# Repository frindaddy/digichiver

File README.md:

# Digichiver

Digichiver is an open hardware and software platform used for operation and 
archiving the audio output of the National Semiconductor MM54104 Mozer 
Digitalker speech synthesis system. The board can drive a physical MM54104,
serve historical speech ROM images through an RP2354B-based ROM emulator, and
record the resulting audio to a microSD card. Archived audio outputs are
available in the [Digitalker audio archive repository](https://github.com/frindaddy/digitalker-audio-archive).

## Repository Layout

The repository is organized by the part of the project it describes:

- `Hardware/` contains the KiCad schematics, PCB layout, custom footprints,
	fabrication outputs, and hardware design notes. Start with
	[`Hardware/readme.md`](Hardware/readme.md) for the circuit description.
- `Software/` contains the MicroPython firmware modules, ROM images, speech
	dictionaries, and archive configuration. Start with
	[`Software/readme.md`](Software/readme.md) for deployment and operation.
- `Simulation/` contains LTspice simulations for the analog speech filter.
- `DesignDocs/` contains project requirements and system architecture notes.
- `Datasheets/` contains component and reference documentation used by the
	design.
- `LICENSE` contains the project license.

## Using Digichiver

Digichiver requires the assembled board, an MM54104 Digitalker chip, and the
required ROM files for the speech vocabulary being used. The board is powered
and programmed over USB-C. Install the supplied
`Software/digichiver_firmware.uf2` firmware using the RP2354B USB bootloader,
then copy the required Python modules, ROM images, and JSON dictionaries from
`Software/` to the board's MicroPython filesystem.

After reset, connect to the board's MicroPython REPL. The software starts an
interactive `digichiver>` command loop for loading ROMs, speaking words,
checking word indexes, and archiving ROM groups to an inserted microSD card.
The complete command reference and file-deployment requirements are documented
in [`Software/readme.md`](Software/readme.md).

The hardware design can be opened with KiCad. The firmware `digitalker_firmware.u2f`
targets MicroPython on the RP2354B.

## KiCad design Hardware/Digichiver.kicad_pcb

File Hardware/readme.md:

# Circuit Description

The doc describes the digichicver circuit schematic (and PCB layout, when needed).

## Block Diagram

This sheet show the block diagram for the Digichiver board. The sheet is broken into 4 sections, the USB-C power/data connector, the Control block, the Digitalker block, the Audio block, and the Power block.

The USB-C connector is setup for a USB 2.0 full-speed connection, as that is the max capability of the RP2354B. Two $5.1k\Omega$ resistors tie `CC1` and `CC2` to ground to specify that this board is a power sink, per the USB specification. This advertises that this board can consume a maximum of 2.5W (5V@500mA).

## Control

This sheet shows the RP2354B and microSD card, as well as their supporting circuitry and pinouts.

### RP2354B

The RP2354B is the MCU on the Digichiver board and is used to control the MM54104 Digitalker chip, emulate Digitalker ROM modules, and record the Digitalker output audio to the microSD card (plus other basic GPIO functions). It interfaces with the MM54104 Digitalker chip, microSD card, and the PCM1809 audio recorder. The RP2354B has 2MB of internal flash in chip, so an external flash module is not required for operation.

#### RP2354B Power and Decoupling

The RP2354B nominally runs off a +3V3 supply, but requires a +1V1 rail for internal functions. Unlike its predecessor (the RP2340), the RP2354B ships with a built in switching regulator to generate this +1V1 rail in package, with the help of some supporting components. The design and layout of this power supply is strictly defined in [Hardware Design with the RP2350](https://pip-assets.raspberrypi.com/categories/1214-rp2350/documents/RP-008280-DS-1-hardware-design-with-rp2350.pdf), and the design recommendations were replicated here (part selection, connections, and layout).

Decoupling capacitors were placed based on the recommendations of [Hardware Design with the RP2350](https://pip-assets.raspberrypi.com/categories/1214-rp2350/documents/RP-008280-DS-1-hardware-design-with-rp2350.pdf); one for each power pin, and a special 4.7uF bulk cap for the +1V1 rail.

#### RP2354B USB Connection

The RP2354B is only capable of USB full speed (USB 2.0, 12Mbps, 48MHz clock). Though this is pretty slow speed, an attempt was made to keep the characteristic impedance of the USB traces close to the USB specification of $90\Omega$, differential. This board isn't being built with controlled impedances, so *rough* numbers are used for the calculation. To find the required trace width for a $90\Omega$ differential impedance, $Z_d$, we use the edge-coupled microstrip impedance equation.

$$Z_d \approx \frac{174}{\sqrt{\epsilon_r + 1.41}} \times \ln(\frac{5.98h}{0.8w + t}) \times [1-0.48^{-0.96\frac{s}{h}}]$$

where $Z_d$ is the differential impedance, $t$ is the trace thickness, $h$ is the height of the dielectric between the microstrip and ground plane, $s$ is the trace spacing, $\epsilon_r$ is the dielectric constant of the material, and $w$ is the trace width. The rough numbers are derived from the general JLCPCB 4 layer TG135 stackup and their manufacturing capabilities: $Z_d = 90\Omega$, $t = 1oz/ft^2$, $h = 8.283mil$, $s = 10mil$, and $\epsilon_r = 4.5$. Using these numbers, we calulate that the ideal trace width to achieve a $90\Omega$ differential impedance is `12.3645mil`.

$27\Omega$ series termination resistors are placed on the USB lines close to the RP2354B to meet the USB impedance specification.

#### RP2354B Clock

The RP2354B does not need an external clock to function (it ships with an internal oscillator), but a stable external frequency source greatly improves peripheral reliability and performance. As such, an external 12MHz crystal oscillator is used to clock the RP2354B. Part selection and circuit design are from the recommendations in [Hardware Design with the RP2350](https://pip-assets.raspberrypi.com/categories/1214-rp2350/documents/RP-008280-DS-1-hardware-design-with-rp2350.pdf).

#### Programming and Reset

Two pushbuttons, `SW1` and `SW2` are used to program and reset the RP2354B, respectively. When `SW1` is pressed on power up, the `QSPI_SS` line to the RP2354B is driven low, placing the device into programming mode. It will show up as a USB storage device, and a bootloader can be loaded into internal memory.

During operation, `SW2` can be pressed to reset the RP2354B by driving the `RUN` pin low.

#### Interfaces and GPIO

The MM54104 Digitalker control and ROM emulation busses take up most of the GPIO pins on the RP2354B. These signals are broken out as follows:

MM54104 Control Signals

| Signal | I/O | Pin Count |
| ------ | --- | --------- |
| SPC Word Selection Bus | O | 8 |
| SPC Chip Select | O | 1 |
| SPC Command Select | O | 1 |
| SPC Write Strobe | O | 1 |
| SPC Interrupt | I | 1 |

MM54104 ROM Emulation

| Signal | I/O | Pin Count |
| ------ | --- | --------- |
| ROM Address Bus | I | 14 |
| ROM Data Bus | O | 8 |
| ROMEN | I | 1 |

Because the MM54104 operates on +5V logic levels, these signals require level shifting. The level shifters are found on the Digitalker sheet.

An I2S interface connects the PCM1809 audio ADC to the RP2354B.

An SPI interface connects the RP2354B to the microSD card port.

One pushbutton, one green "Ready" LED, and one yellow "Activity" LED are connected to the RP2354B as GPIO.

### microSD Card

The RP2354B has an SPI connection to the microSD card header. An SPI connection was selected over the typical SDIO connection for a few reasons: all microSD cards support SPI communication, the higher speeds of the SDIO interface are not required for this application, and the SPI interface requries 4 pins instead of 6. The SPI bus connects to the SPI1 peripheral on the RP2354B, per the [RP2354B datasheet](https://pip-assets.raspberrypi.com/categories/1214-rp2350/documents/RP-008373-DS-2-rp2350-datasheet.pdf). 10k pullup resistors are added on each SPI line to keep the bus in a known state on bootup.

The card detect line `SD_DET` is routed as a GPIO input to the RP2354B to check if a microSD card is actually inserted before writing to it. The physical mechanism in the microSD card slot is a mechanical switch that connects pin `9` to pin `10` when a card is inserted into the slot ([per DM3AT-SF-PEJM5 datasheet](https://www.hirose.com/product/document?clcode=CL0609-0033-6-00&productname=DM3AT-SF-https://www.hirose.com/product/document?clcode=CL0609-0033-6-00&productname=DM3AT-SF-PEJ2M5&series=DM3&documenttype=Catalog&lang=en&documentid=D49662_en)). When a card is not installed, the `SD_DET` line is pulled low by `R32`. When a microSD card is inserted into the slot, the `SD_DET` line is driven high to +3V3.

## Digitalker

This sheet shows the MM54104 Digitalker Speech Processing Chip IC socket (`XC1`), required level shifting, and speech output filtering.

### MM54104

The MM54104 is designed to be socketed on the board, rather than soldered directly. This helps protect the rare MM54104 from any soldering induced temperature stress, and keeps it easily replaceable in the case of failure due to age.

The MM54104 is powered by +9V, with a 100nF decoupling capacitor placed close to the power input pin.

The MM54104 requires an external 4MHz clock for operation. Rather than add additonal components to the BOM, the `OSC_IN` pin is connected to one of the RP2354B PWM output ports through a level shifter. The 4MHz clock is generated by the RP2354B PWM controller.

### Level Shifting

The MM54104 runs on a +7-11V power input, although uses +5V compatable TTL logic for its I/O connections. As such, level shifting is required between the +3V3 CMOS I/O from the RP2354B and the +5V TTL logic from the MM54104. This level shifting is accomplished using two different part numbers.

For the MM54104 → RP2354B connections, the SN74LVC245A is used. This level shifter operates on a single +3V3 rail, but has +5V tolerant inputs. This single supply architecture not only simplifies the power plane routing on the board, but also reduces the total input capacitance on the +5V rail[^1]. A total of two are required to shift the `ROM_ADDR[0..13]`, `ROMEN`, and `INTR` lines. The SN74LVC245As are configured as always enabled, A → B mode.

[^1]: The reduction of input capacitance is beneficial as the USB specification states that power sinking devices should have no more than 10uF of input capacitance on the +5V power rail to limit inrush current and prevent damaging the power sourcing device. With some quick napkin math, one can determine that this board nominally has 11.3uF of input capacitance on the +5V rail, plus whatever parasitic capacitance is added from the traces in the layout. Looking at the decoupling and bulk capacitors used on the +5V rail, the 10uF cap (`C31`) is $\pm$20%, and the 1uF cap (`C33`) and 100nF caps (`C5`, `C6`, `C7`) are $\pm$10%, therefore worst case input capacitance is `13.43uF`, plus whatever parasitic capacitance exists. After testing the board in real life, this doesn't seem to be a problem.  

For the RP2354B → MM54104 connections, the SN74LVCBT245 is used. This level shifter operates on split +3V3 and +5V rails. A total of three are required to shift the `DIGITALKER_CLK_4MHZ`, `DIGITALKER_CS`, `DIGITALKER_WR`, `DIGITALKER_CMS`, `SW[1..8]`, and `RDATA[0..7]` lines. The SN74LVCBT245s are configured as always enabled, A → B mode.

### Speech Output Filter

The speech output filter is designed to produce the maximum frequency response for the MM54104 speech output. It features a voltage rebiasing network to shift the output down to +3V3 tolerant levels, and a dual-stage Sallen-Key filter to match the filtering recommendations in the DT1050 datasheet.

First, a 1uF input capacitor is used to decouple the audio stream from the ~+4VDC "silence voltage" output by the MM54104. The audio stream is then rebiased to a +1V65 DC voltage offset through a pullup resistor (`R23`) to `V_BIAS`, which is generated with a 2:1 voltage divider. A 100nF decoupling capactior (`C42`) is used to keep `V_BIAS` clean from any switching noise that may exist on the +3V3 rail. The rebiased audio output then goes through the first Sallen-Key filter, which is a 7,234Hz low pass filter. The output of the low-pass filter goes into the next Sallen-Key filter, a 194Hz high-pass filter. Combined, the rebiasing and filtering produce the a similar frequency response to that recommended by the D1050 datasheet.

LTSpice simulations for this filtering circuit can be found in `Digichiver/Simulation`.

## Audio

This sheet contains the three audio output sources (audio ADC, 3.5mm jack, and onboard speaker) and their associated circuitry. All outputs are AC coupled to the filtered speech line through 1uF capacitors.

### Audio ADC

To record the audio stream to the microSD card, the RP2354B requires an external audio ADC connected via an I2S bus. The PCM1809 is used for this.

The PCM1809 has two stereo inputs, but the MM54104 produces only a single mono output. As such, only the positive input on channel 1 of the PCM1809 is connected, with the channel 1 negative input and both channel 2 inputs capacitively coupled to ground, per [the PCM1809 datasheet](https://www.ti.com/lit/ds/symlink/pcm1809.pdf?ts=1723810813788).

The PCM1809 is configured in I2S target mode, therefore the RP2354B controls the bus/chip. The RP2354B generates the `BCLK` and `FSYNC` signals, and the PCM1809 dynamically adjusts its sampling rate based on the `BCLK` to `FSYNC` ratio. The output data is sent on the `SDATA` line.

Decoupling capacitors are selected based on the typical application in [the PCM1809 datasheet](https://www.ti.com/lit/ds/symlink/pcm1809.pdf?ts=1723810813788).

### 3.5mm Jack

The 3.5mm jack provides an output source to external speaker amplifiers, if desired. To make the mono audio signal compatable with a stereo TRS jack, the audio is split to the tip (`T`) and ring (`R`) pins of the jack through $100\Omega$ resistors. The resistors prevent dead shorts between the T and R pins if a non TRS cable is inserted into the jack. A $100k\Omega$ resistor weakly pulls the line to ground to help prevent popping on cable connection/disconnection.

### Onboard Speaker

The onboard speaker `LS1` is driven using a stereo class-D amplifier IC, the PAM8302A. This amplifier is capable of driving an $8\Omega$ speaker at just under 800mW when powered by a +3V3 rail. As such, the $8\Omega$ 780mW CMS-2821-078T onboard speaker is a solid choice due to its matching specifications and reasonbly even frequency response.

Because the PAM8302A expects a stereo input, the mono MM54014 output is fed into the positive input channel and the negative input channel is capacitively coupled to ground.

`RV1` is a $10k\Omega$ logarithmic potentiometer used to control the ultimate volume of the onboard speaker.

A GPIO line `SPEAKER_MUTE` is routed to the RP2354B so the speaker can be disabled by software, when required.

## Power

This sheet shows the two switching power supplies responsible for deriving the +3V3 and +9V power rails from the +5V input rail. Both designs are based on a combination of the typical application diagrams in their respective datasheets and designs generated using the Texas Instruments [WEBENCH® Power Designer](https://webench.ti.com/power-designer/) tool.

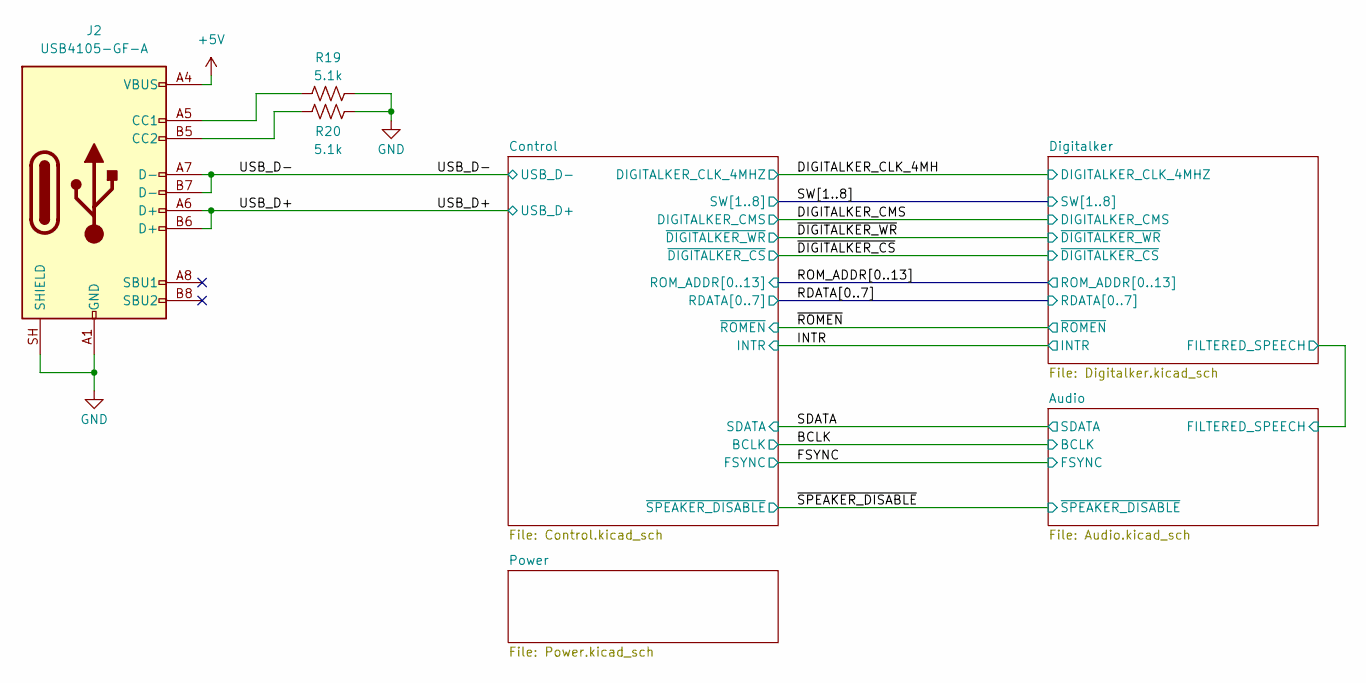
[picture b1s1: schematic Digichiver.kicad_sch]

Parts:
J2: USB4105-GF-A; USB_C_Receptacle_GCT_USB4105-xx-A_16P_TopMnt_Horizontal; MPN USB4105-GF-A; JLCPCB Part # C3020560
R19, R20: 5.1k; R_0402_1005Metric; MPN 0402WGF5101TCE; JLCPCB Part # C25905

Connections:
+5V: J2.A4 (VBUS), J2.A9 (VBUS), J2.B4 (VBUS), J2.B9 (VBUS); also elsewhere on the board
/USB_D+: J2.A6 (D+), J2.B6 (D+); also elsewhere on the board
/USB_D-: J2.A7 (D-), J2.B7 (D-); also elsewhere on the board
GND: J2.A1 (GND), J2.A12 (GND), J2.B1 (GND), J2.B12 (GND), J2.SH (SHIELD), R19.1, R20.1; also elsewhere on the board
unnamed: J2.A5 (CC1), R19.2
unnamed: J2.B5 (CC2), R20.2

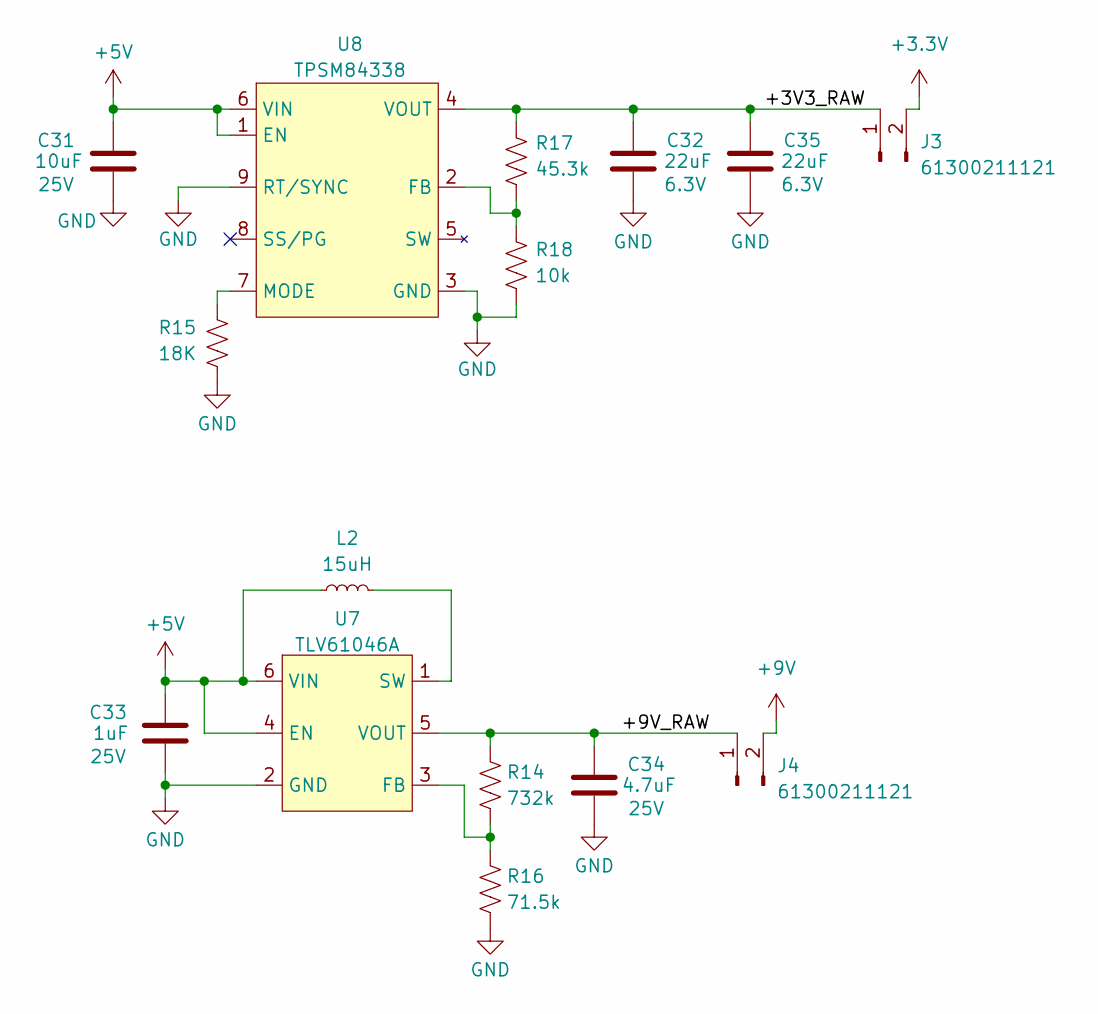
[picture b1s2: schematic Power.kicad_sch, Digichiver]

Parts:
C31: 10uF; C_0603_1608Metric; Voltage 25V; MPN CL10A106MA8NRNC; JLCPCB Part # C96446
C32, C35: 22uF; C_0603_1608Metric; Voltage 6.3V; MPN CL10A226MQ8NRNC; JLCPCB Part # C59461
C33: 1uF; C_0402_1005Metric; Voltage 25V; MPN CL05A105KA5NQNC; JLCPCB Part # C52923
C34: 4.7uF; C_0805_2012Metric; Voltage 25V; MPN CL21A475KAQNNNE; JLCPCB Part # C1779
J3, J4: 61300211121; PinHeader_1x02_P2.54mm_Vertical; MPN 61300211121; JLCPCB Part # C2915055
L2: 15uH; IND_VLCF4020T-150MR68; MPN VLCF4020T-150MR68; JLCPCB Part # C695173
R14: 732k; R_0402_1005Metric; MPN RC0402FR-07732KL; JLCPCB Part # C137940
R15: 18K; R_0402_1005Metric; MPN 0402WGF1802TCE; JLCPCB Part # C25762
R16: 71.5k; R_0402_1005Metric; MPN RC0402FR-0771K5L; JLCPCB Part # C273328
R17: 45.3k; R_0402_1005Metric; MPN RC0402FR-0745K3L; JLCPCB Part # C137977
R18: 10k; R_0402_1005Metric; MPN 0402WGF1002TCE; JLCPCB Part # C25744
U7: TLV61046A; SOT-23-6; MPN TLV61046A; JLCPCB Part # C139398
U8: TPSM84338; CONV_TPSM84338RCJR; MPN TPSM84338; JLCPCB Part # C47122151

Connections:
+3.3V: J3.2; also elsewhere on the board
+5V: C31.1, C33.1, L2.1, U7.4 (EN), U7.6 (VIN), U8.1 (EN), U8.6 (VIN); also elsewhere on the board
+9V: J4.2; also elsewhere on the board
/Power/+3V3_RAW: C32.1, C35.1, J3.1, R17.1, U8.4 (VOUT)
/Power/+9V_RAW: C34.1, J4.1, R14.1, U7.5 (VOUT)
GND: C31.2, C32.2, C33.2, C34.2, C35.2, R15.2, R16.2, R18.2, U7.2 (GND), U8.3 (GND), U8.9 (RT/SYNC); also elsewhere on the board
unnamed: R14.2, R16.1, U7.3 (FB)
unnamed: L2.2, U7.1 (SW)
unnamed: R17.2, R18.1, U8.2 (FB)
unnamed: R15.1, U8.7 (MODE)

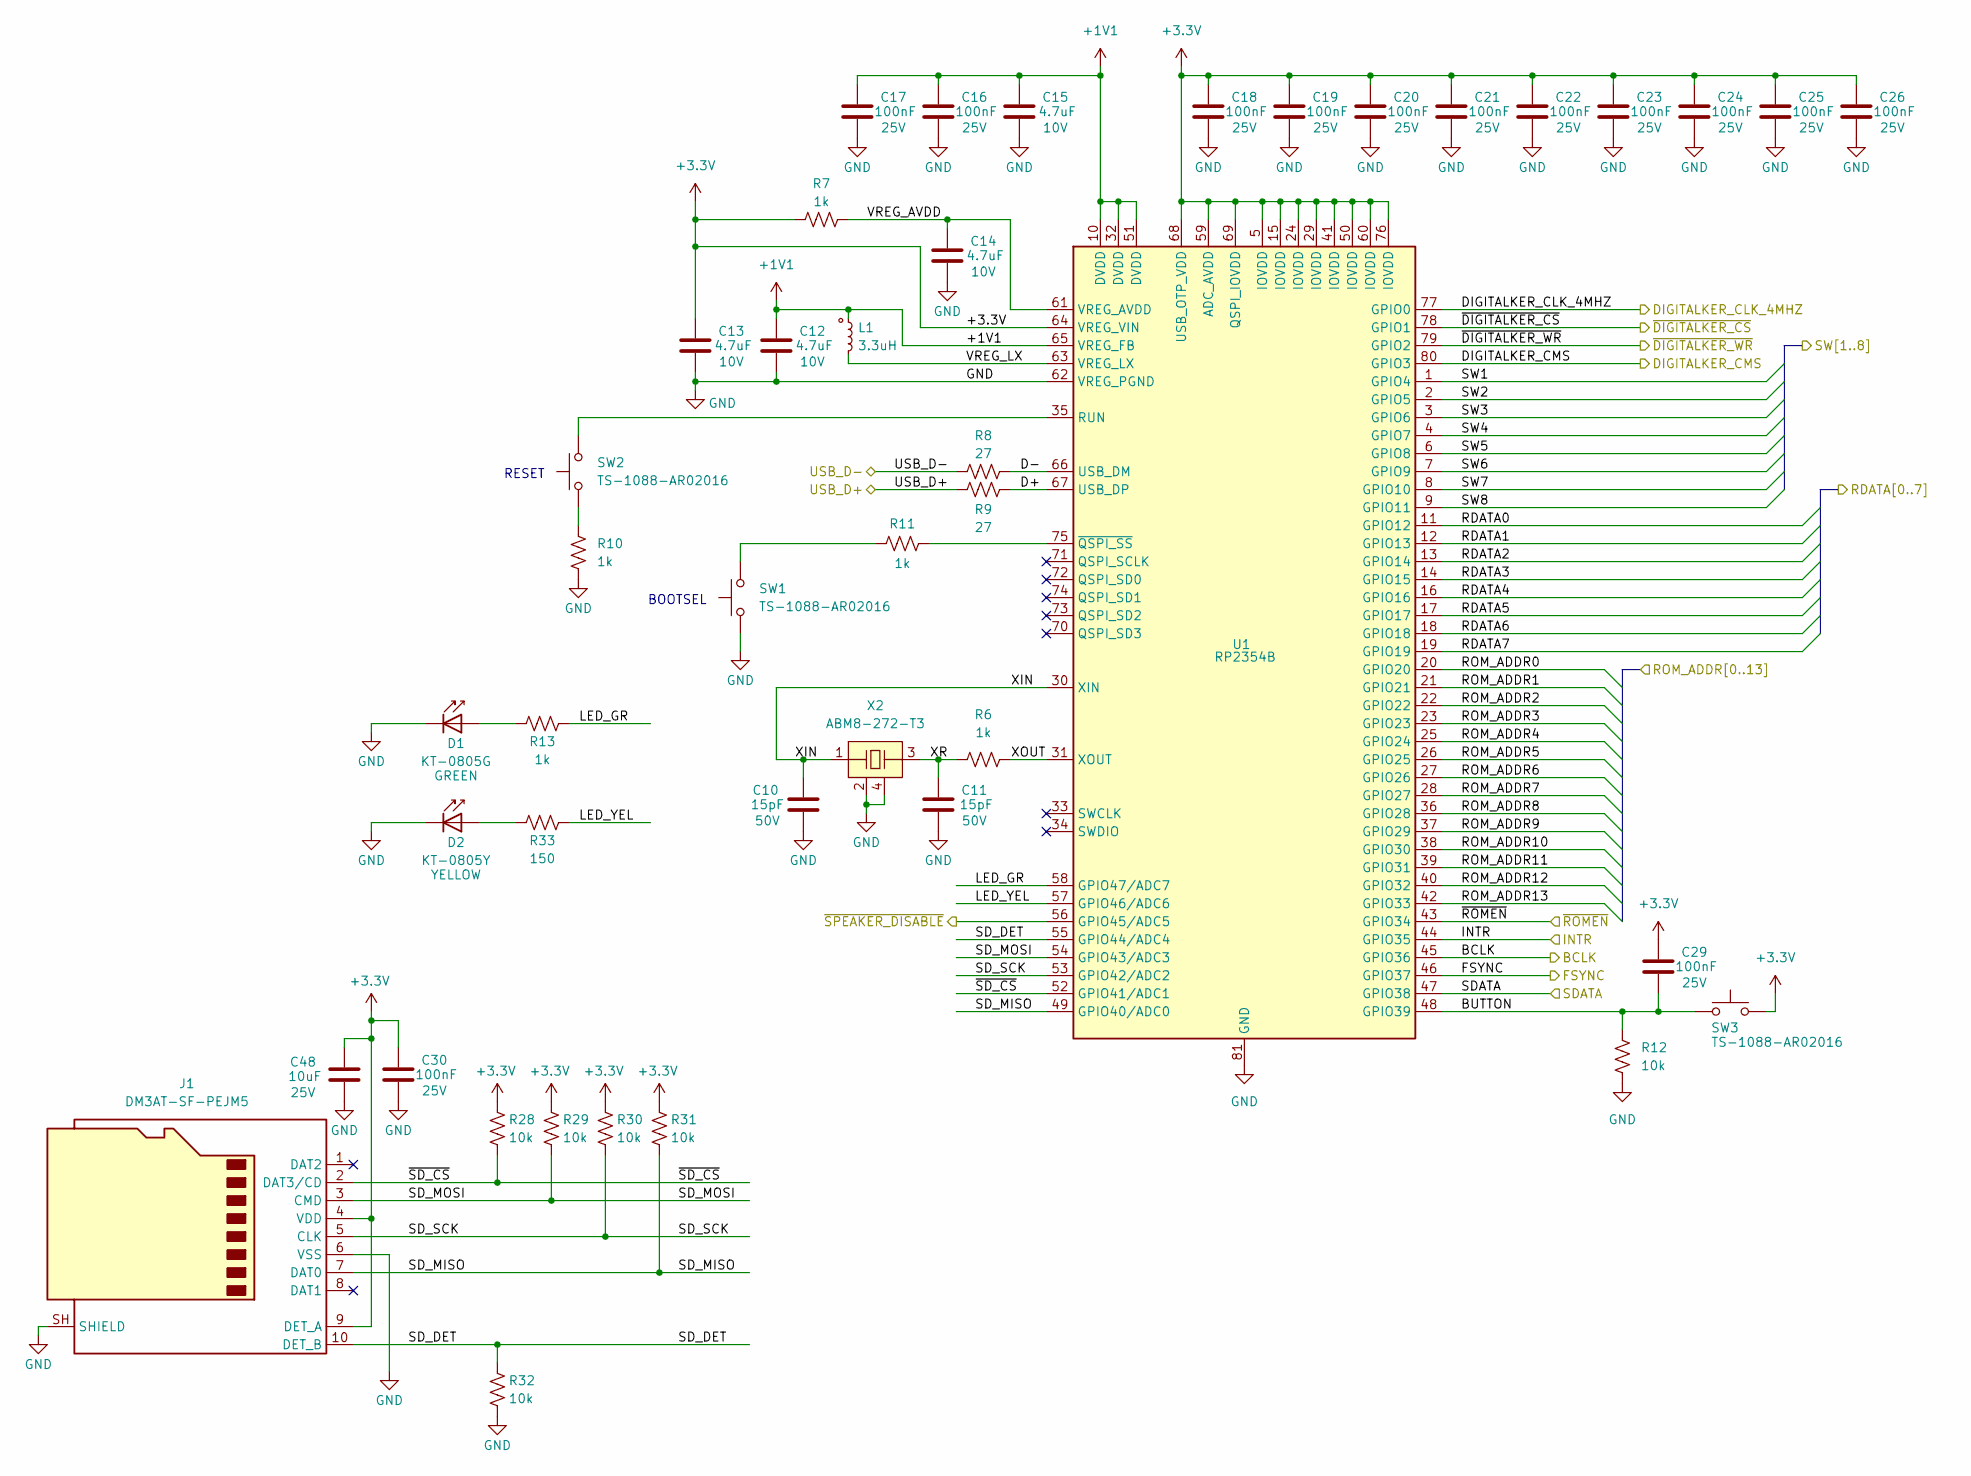
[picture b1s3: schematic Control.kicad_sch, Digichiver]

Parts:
C10, C11: 15pF; C_0402_1005Metric; Voltage 50V; MPN 0402CG150J500NT; JLCPCB Part # C1548
C12, C13, C14, C15: 4.7uF; C_0402_1005Metric; Voltage 10V; MPN CL05A475MP5NRNC; JLCPCB Part # C23733
C16, C17, C18, C19, C20, C21, C22, C23, C24, C25, C26, C29, C30: 100nF; C_0402_1005Metric; Voltage 25V; MPN CL05B104KB54PNC; JLCPCB Part # C307331
C48: 10uF; C_0603_1608Metric; Voltage 25V; MPN CL10A106MA8NRNC; JLCPCB Part # C96446
D1: KT-0805G; LED_0805_2012Metric; MPN KT-0805G; JLCPCB Part # C2297
D2: KT-0805Y; LED_0805_2012Metric; MPN KT-0805Y; JLCPCB Part # C2296
J1: DM3AT-SF-PEJM5; microSD_HC_Hirose_DM3AT-SF-PEJM5; MPN DM3AT-SF-PEJM5; JLCPCB Part # C114218
L1: 3.3uH; L_0805_2012Metric; MPN AOTA-B201610S3R3-101-T; JLCPCB Part # C42411119
R6, R7, R10, R11, R13: 1k; R_0402_1005Metric; MPN 0402WGF1001TCE; JLCPCB Part # C11702
R8, R9: 27; R_0603_1608Metric; MPN 0603WAF270JT5E; JLCPCB Part # C25190
R12, R28, R29, R30, R31, R32: 10k; R_0402_1005Metric; MPN 0402WGF1002TCE; JLCPCB Part # C25744
R33: 150; R_0402_1005Metric; MPN 0402WGF1500TCE; JLCPCB Part # C25082
SW1, SW2, SW3: TS-1088-AR02016; SW_SPST_TS-1088-xR020; MPN TS-1088-AR02016; JLCPCB Part # C720477
U1: RP2354B; QFN-80-1EP_10x10mm_P0.4mm_EP3.4x3.4mm; MPN RP2354B; JLCPCB Part # C39843328
X2: ABM8-272-T3; Crystal_SMD_Abracon_ABM8G-4Pin_3.2x2.5mm; MPN ABM8-272-T3; JLCPCB Part # C20625731

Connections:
+1V1: C12.1, C15.1, C16.1, C17.1, L1.1, U1.10 (DVDD), U1.32 (DVDD), U1.51 (DVDD), U1.65 (VREG_FB)
+3.3V: C13.1, C18.1, C19.1, C20.1, C21.1, C22.1, C23.1, C24.1, C25.1, C26.1, C29.1, C30.1, C48.1, J1.4 (VDD), J1.9 (DET_A), R7.2, R28.2, R29.2, R30.2, R31.2, SW3.2, U1.5 (IOVDD), U1.15 (IOVDD), U1.24 (IOVDD), U1.29 (IOVDD), U1.41 (IOVDD), U1.50 (IOVDD), U1.59 (ADC_AVDD), U1.60 (IOVDD), U1.64 (VREG_VIN), U1.68 (USB_OTP_VDD), U1.69 (QSPI_IOVDD), U1.76 (IOVDD); also elsewhere on the board
/BCLK: U1.45 (GPIO36); also elsewhere on the board
/Control/BUTTON: C29.2, R12.1, SW3.1, U1.48 (GPIO39)
/Control/D+: R9.1, U1.67 (USB_DP)
/Control/D-: R8.1, U1.66 (USB_DM)
/Control/LED_GR: R13.1, U1.58 (GPIO47/ADC7)
/Control/LED_YEL: R33.1, U1.57 (GPIO46/ADC6)
/Control/SD_DET: J1.10 (DET_B), R32.2, U1.55 (GPIO44/ADC4)
/Control/SD_MISO: J1.7 (DAT0), R31.1, U1.49 (GPIO40/ADC0)
/Control/SD_MOSI: J1.3 (CMD), R29.1, U1.54 (GPIO43/ADC3)
/Control/SD_SCK: J1.5 (CLK), R30.1, U1.53 (GPIO42/ADC2)
/Control/VREG_AVDD: C14.1, R7.1, U1.61 (VREG_AVDD)
/Control/VREG_LX: L1.2, U1.63 (VREG_LX)
/Control/XIN: C10.1, U1.30 (XIN), X2.1
/Control/XOUT: R6.1, U1.31 (XOUT)
/Control/XR: C11.1, R6.2, X2.3
/Control/~SD_CS: J1.2 (DAT3/CD), R28.1, U1.52 (GPIO41/ADC1)
/DIGITALKER_CLK_4MH: U1.77 (GPIO0); also elsewhere on the board
/DIGITALKER_CMS: U1.80 (GPIO3); also elsewhere on the board
/FSYNC: U1.46 (GPIO37); also elsewhere on the board
/INTR: U1.44 (GPIO35); also elsewhere on the board
/RDATA0: U1.11 (GPIO12); also elsewhere on the board
/RDATA1: U1.12 (GPIO13); also elsewhere on the board
/RDATA2: U1.13 (GPIO14); also elsewhere on the board
/RDATA3: U1.14 (GPIO15); also elsewhere on the board
/RDATA4: U1.16 (GPIO16); also elsewhere on the board
/RDATA5: U1.17 (GPIO17); also elsewhere on the board
/RDATA6: U1.18 (GPIO18); also elsewhere on the board
/RDATA7: U1.19 (GPIO19); also elsewhere on the board
/ROM_ADDR0: U1.20 (GPIO20); also elsewhere on the board
/ROM_ADDR1: U1.21 (GPIO21); also elsewhere on the board
/ROM_ADDR2: U1.22 (GPIO22); also elsewhere on the board
/ROM_ADDR3: U1.23 (GPIO23); also elsewhere on the board
/ROM_ADDR4: U1.25 (GPIO24); also elsewhere on the board
/ROM_ADDR5: U1.26 (GPIO25); also elsewhere on the board
/ROM_ADDR6: U1.27 (GPIO26); also elsewhere on the board
/ROM_ADDR7: U1.28 (GPIO27); also elsewhere on the board
/ROM_ADDR8: U1.36 (GPIO28); also elsewhere on the board
/ROM_ADDR9: U1.37 (GPIO29); also elsewhere on the board
/ROM_ADDR10: U1.38 (GPIO30); also elsewhere on the board
/ROM_ADDR11: U1.39 (GPIO31); also elsewhere on the board
/ROM_ADDR12: U1.40 (GPIO32); also elsewhere on the board
/ROM_ADDR13: U1.42 (GPIO33); also elsewhere on the board
/SDATA: U1.47 (GPIO38); also elsewhere on the board
/SW1: U1.1 (GPIO4); also elsewhere on the board
/SW2: U1.2 (GPIO5); also elsewhere on the board
/SW3: U1.3 (GPIO6); also elsewhere on the board
/SW4: U1.4 (GPIO7); also elsewhere on the board
/SW5: U1.6 (GPIO8); also elsewhere on the board
/SW6: U1.7 (GPIO9); also elsewhere on the board
/SW7: U1.8 (GPIO10); also elsewhere on the board
/SW8: U1.9 (GPIO11); also elsewhere on the board
/USB_D+: R9.2; also elsewhere on the board
/USB_D-: R8.2; also elsewhere on the board
/~DIGITALKER_CS: U1.78 (GPIO1); also elsewhere on the board
/~DIGITALKER_WR: U1.79 (GPIO2); also elsewhere on the board
/~ROMEN: U1.43 (GPIO34); also elsewhere on the board
/~SPEAKER_DISABLE: U1.56 (GPIO45/ADC5); also elsewhere on the board
GND: C10.2, C11.2, C12.2, C13.2, C14.2, C15.2, C16.2, C17.2, C18.2, C19.2, C20.2, C21.2, C22.2, C23.2, C24.2, C25.2, C26.2, C30.2, C48.2, D1.1 (K), D2.1 (K), J1.6 (VSS), J1.SH (SHIELD), R10.1, R12.2, R32.1, SW1.1, U1.62 (VREG_PGND), U1.81 (GND), X2.2, X2.4; also elsewhere on the board
unnamed: D1.2 (A), R13.2
unnamed: D2.2 (A), R33.2
unnamed: R10.2, SW2.1
unnamed: R11.2, SW1.2
unnamed: SW2.2, U1.35 (RUN)
unnamed: R11.1, U1.75 (~QSPI_SS)

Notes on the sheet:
RESET
BOOTSEL

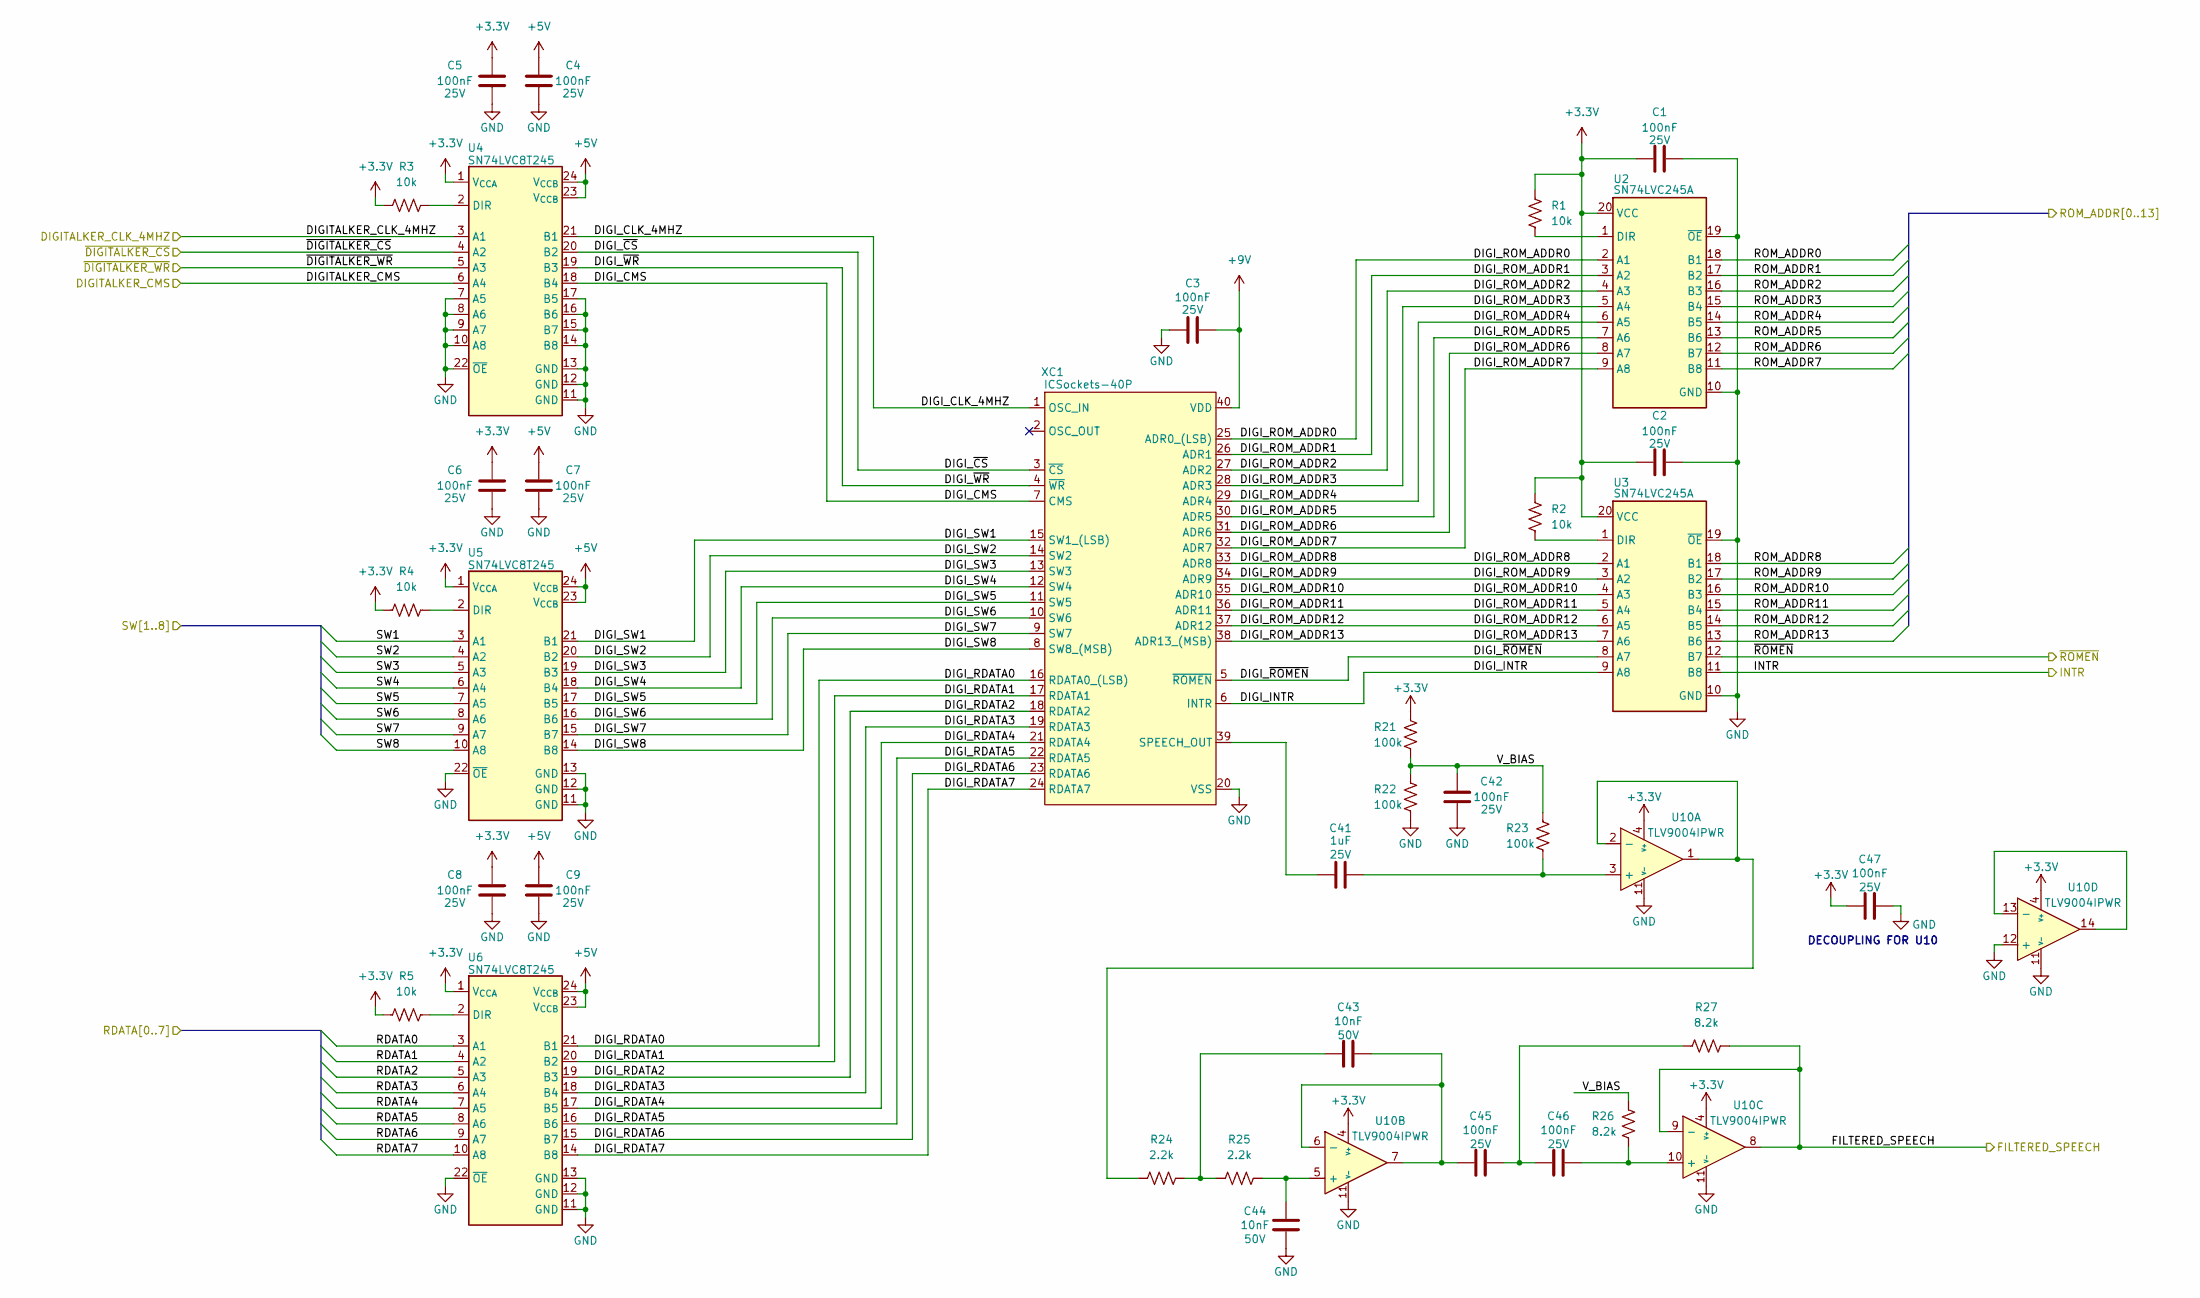
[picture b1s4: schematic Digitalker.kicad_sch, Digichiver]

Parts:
C1, C2, C3, C4, C5, C6, C7, C8, C9, C42, C45, C46, C47: 100nF; C_0402_1005Metric; Voltage 25V; MPN CL05B104KB54PNC; JLCPCB Part # C307331
C41: 1uF; C_0402_1005Metric; Voltage 25V; MPN CL05A105KA5NQNC; JLCPCB Part # C52923
C43, C44: 10nF; C_0402_1005Metric; Voltage 50V; MPN CL05B103KB5NNNC; JLCPCB Part # C15195
R1, R2, R3, R4, R5: 10k; R_0402_1005Metric; MPN 0402WGF1002TCE; JLCPCB Part # C25744
R21, R22, R23: 100k; R_0402_1005Metric; MPN 0402WGF1003TCE; JLCPCB Part # C25741
R24, R25: 2.2k; R_0402_1005Metric; MPN 0402WGF2201TCE; JLCPCB Part # C25879
R26, R27: 8.2k; R_0402_1005Metric; MPN 0402WGF8201TCE; JLCPCB Part # C25924
U2, U3: SN74LVC245A; TSSOP-20_4.4x6.5mm_P0.65mm; MPN SN74LVC245APWR; JLCPCB Part # C7848
U4, U5, U6: SN74LVC8T245; TSSOP-24_4.4x7.8mm_P0.65mm; MPN SN74LVC8T245PWR; JLCPCB Part # C27643
U10: TLV9004IPWR; TSSOP-14_4.4x5mm_P0.65mm; MPN TLV9004IPWR; JLCPCB Part # C2058050
XC1: ICSockets-40P; DIP-40_W15.24mm_Socket; MPN ICSockets-40P; JLCPCB Part # C2332

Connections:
+3.3V: C1.2, C2.2, C5.1, C6.1, C8.1, C47.2, R1.2, R2.2, R3.2, R4.2, R5.2, R21.2, U2.20 (VCC), U3.20 (VCC), U4.1 (V_{CCA}), U5.1 (V_{CCA}), U6.1 (V_{CCA}), U10.4 (V+); also elsewhere on the board
+5V: C4.1, C7.1, C9.1, U4.23 (V_{CCB}), U4.24 (V_{CCB}), U5.23 (V_{CCB}), U5.24 (V_{CCB}), U6.23 (V_{CCB}), U6.24 (V_{CCB}); also elsewhere on the board
+9V: C3.1, XC1.40 (VDD); also elsewhere on the board
/DIGITALKER_CLK_4MH: U4.3 (A1); also elsewhere on the board
/DIGITALKER_CMS: U4.6 (A4); also elsewhere on the board
/Digitalker/DIGI_CLK_4MHZ: U4.21 (B1), XC1.1 (OSC_IN)
/Digitalker/DIGI_CMS: U4.18 (B4), XC1.7 (CMS)
/Digitalker/DIGI_INTR: U3.9 (A8), XC1.6 (INTR)
/Digitalker/DIGI_RDATA0: U6.21 (B1), XC1.16 (RDATA0_(LSB))
/Digitalker/DIGI_RDATA1: U6.20 (B2), XC1.17 (RDATA1)
/Digitalker/DIGI_RDATA2: U6.19 (B3), XC1.18 (RDATA2)
/Digitalker/DIGI_RDATA3: U6.18 (B4), XC1.19 (RDATA3)
/Digitalker/DIGI_RDATA4: U6.17 (B5), XC1.21 (RDATA4)
/Digitalker/DIGI_RDATA5: U6.16 (B6), XC1.22 (RDATA5)
/Digitalker/DIGI_RDATA6: U6.15 (B7), XC1.23 (RDATA6)
/Digitalker/DIGI_RDATA7: U6.14 (B8), XC1.24 (RDATA7)
/Digitalker/DIGI_ROM_ADDR0: U2.2 (A1), XC1.25 (ADR0_(LSB))
/Digitalker/DIGI_ROM_ADDR1: U2.3 (A2), XC1.26 (ADR1)
/Digitalker/DIGI_ROM_ADDR2: U2.4 (A3), XC1.27 (ADR2)
/Digitalker/DIGI_ROM_ADDR3: U2.5 (A4), XC1.28 (ADR3)
/Digitalker/DIGI_ROM_ADDR4: U2.6 (A5), XC1.29 (ADR4)
/Digitalker/DIGI_ROM_ADDR5: U2.7 (A6), XC1.30 (ADR5)
/Digitalker/DIGI_ROM_ADDR6: U2.8 (A7), XC1.31 (ADR6)
/Digitalker/DIGI_ROM_ADDR7: U2.9 (A8), XC1.32 (ADR7)
/Digitalker/DIGI_ROM_ADDR8: U3.2 (A1), XC1.33 (ADR8)
/Digitalker/DIGI_ROM_ADDR9: U3.3 (A2), XC1.34 (ADR9)
/Digitalker/DIGI_ROM_ADDR10: U3.4 (A3), XC1.35 (ADR10)
/Digitalker/DIGI_ROM_ADDR11: U3.5 (A4), XC1.36 (ADR11)
/Digitalker/DIGI_ROM_ADDR12: U3.6 (A5), XC1.37 (ADR12)
/Digitalker/DIGI_ROM_ADDR13: U3.7 (A6), XC1.38 (ADR13_(MSB))
/Digitalker/DIGI_SW1: U5.21 (B1), XC1.15 (SW1_(LSB))
/Digitalker/DIGI_SW2: U5.20 (B2), XC1.14 (SW2)
/Digitalker/DIGI_SW3: U5.19 (B3), XC1.13 (SW3)
/Digitalker/DIGI_SW4: U5.18 (B4), XC1.12 (SW4)
/Digitalker/DIGI_SW5: U5.17 (B5), XC1.11 (SW5)
/Digitalker/DIGI_SW6: U5.16 (B6), XC1.10 (SW6)
/Digitalker/DIGI_SW7: U5.15 (B7), XC1.9 (SW7)
/Digitalker/DIGI_SW8: U5.14 (B8), XC1.8 (SW8_(MSB))
/Digitalker/DIGI_~CS: U4.20 (B2), XC1.3 (~CS)
/Digitalker/DIGI_~ROMEN: U3.8 (A7), XC1.5 (~ROMEN)
/Digitalker/DIGI_~WR: U4.19 (B3), XC1.4 (~WR)
/Digitalker/FILTERED_SPEECH: R27.1, U10.8, U10.9 (-); also elsewhere on the board
/Digitalker/V_BIAS: C42.1, R21.1, R22.2, R23.2, R26.2
/INTR: U3.11 (B8); also elsewhere on the board
/RDATA0: U6.3 (A1); also elsewhere on the board
/RDATA1: U6.4 (A2); also elsewhere on the board
/RDATA2: U6.5 (A3); also elsewhere on the board
/RDATA3: U6.6 (A4); also elsewhere on the board
/RDATA4: U6.7 (A5); also elsewhere on the board
/RDATA5: U6.8 (A6); also elsewhere on the board
/RDATA6: U6.9 (A7); also elsewhere on the board
/RDATA7: U6.10 (A8); also elsewhere on the board
/ROM_ADDR0: U2.18 (B1); also elsewhere on the board
/ROM_ADDR1: U2.17 (B2); also elsewhere on the board
/ROM_ADDR2: U2.16 (B3); also elsewhere on the board
/ROM_ADDR3: U2.15 (B4); also elsewhere on the board
/ROM_ADDR4: U2.14 (B5); also elsewhere on the board
/ROM_ADDR5: U2.13 (B6); also elsewhere on the board
/ROM_ADDR6: U2.12 (B7); also elsewhere on the board
/ROM_ADDR7: U2.11 (B8); also elsewhere on the board
/ROM_ADDR8: U3.18 (B1); also elsewhere on the board
/ROM_ADDR9: U3.17 (B2); also elsewhere on the board
/ROM_ADDR10: U3.16 (B3); also elsewhere on the board
/ROM_ADDR11: U3.15 (B4); also elsewhere on the board
/ROM_ADDR12: U3.14 (B5); also elsewhere on the board
/ROM_ADDR13: U3.13 (B6); also elsewhere on the board
/SW1: U5.3 (A1); also elsewhere on the board
/SW2: U5.4 (A2); also elsewhere on the board
/SW3: U5.5 (A3); also elsewhere on the board
/SW4: U5.6 (A4); also elsewhere on the board
/SW5: U5.7 (A5); also elsewhere on the board
/SW6: U5.8 (A6); also elsewhere on the board
/SW7: U5.9 (A7); also elsewhere on the board
/SW8: U5.10 (A8); also elsewhere on the board
/~DIGITALKER_CS: U4.4 (A2); also elsewhere on the board
/~DIGITALKER_WR: U4.5 (A3); also elsewhere on the board
/~ROMEN: U3.12 (B7); also elsewhere on the board
GND: C1.1, C2.1, C3.2, C4.2, C5.2, C6.2, C7.2, C8.2, C9.2, C42.2, C44.2, C47.1, R22.1, U2.10 (GND), U2.19 (~OE), U3.10 (GND), U3.19 (~OE), U4.7 (A5), U4.8 (A6), U4.9 (A7), U4.10 (A8), U4.11 (GND), U4.12 (GND), U4.13 (GND), U4.14 (B8), U4.15 (B7), U4.16 (B6), U4.17 (B5), U4.22 (~OE), U5.11 (GND), U5.12 (GND), U5.13 (GND), U5.22 (~OE), U6.11 (GND), U6.12 (GND), U6.13 (GND), U6.22 (~OE), U10.11 (V-), U10.12 (+), XC1.20 (VSS); also elsewhere on the board
unnamed: C43.2, R24.1, R25.2
unnamed: C45.1, C46.2, R27.2
unnamed: R1.1, U2.1 (DIR)
unnamed: R2.1, U3.1 (DIR)
unnamed: R3.1, U4.2 (DIR)
unnamed: R4.1, U5.2 (DIR)
unnamed: R5.1, U6.2 (DIR)
unnamed: C41.1, R23.1, U10.3 (+)
unnamed: R24.2, U10.1, U10.2 (-)
unnamed: C44.1, R25.1, U10.5 (+)
unnamed: C43.1, C45.2, U10.6 (-), U10.7
unnamed: C46.1, R26.1, U10.10 (+)
unnamed: U10.13 (-), U10.14
unnamed: C41.2, XC1.39 (SPEECH_OUT)

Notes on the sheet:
DECOUPLING FOR U10

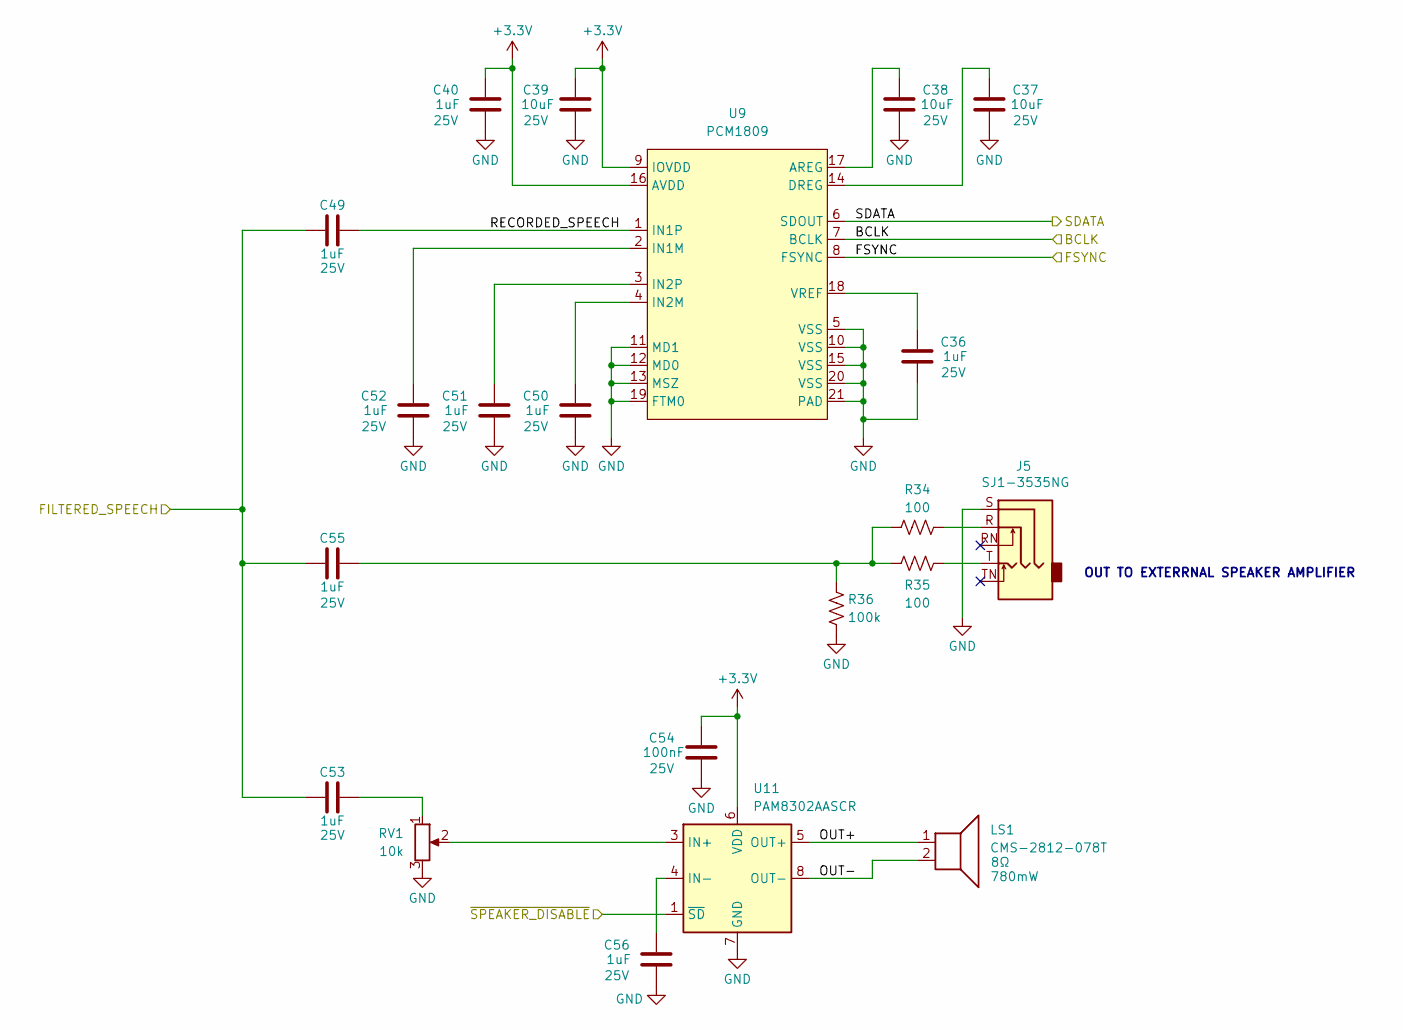
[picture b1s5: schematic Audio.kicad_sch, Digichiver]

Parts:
C36, C40, C49, C50, C51, C52, C53, C55, C56: 1uF; C_0402_1005Metric; Voltage 25V; MPN CL05A105KA5NQNC; JLCPCB Part # C52923
C37, C38, C39: 10uF; C_0603_1608Metric; Voltage 25V; MPN CL10A106MA8NRNC; JLCPCB Part # C96446
C54: 100nF; C_0402_1005Metric; Voltage 25V; MPN CL05B104KB54PNC; JLCPCB Part # C307331
J5: SJ1-3535NG; Jack_3.5mm_CUI_SJ1-3535NG_Horizontal; MPN SJ1-3535NG; JLCPCB Part # C4991610
LS1: CMS-2812-078T; SPKR_CMS-2812-078T; MPN CMS-2812-078T
R34, R35: 100; R_0402_1005Metric; MPN 0402WGF1000TCE; JLCPCB Part # C25076
R36: 100k; R_0402_1005Metric; MPN 0402WGF1003TCE; JLCPCB Part # C25741
RV1: 10k; PTV09; MPN PTV09A-4015F-A103
U9: PCM1809; PCM1820IRTER; MPN PCM1809IRTER; JLCPCB Part # C38558044
U11: PAM8302AASCR; MSOP-8_3x3mm_P0.65mm; MPN PAM8302AASCR; JLCPCB Part # C113367

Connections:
+3.3V: C39.1, C40.1, C54.1, U9.9 (IOVDD), U9.16 (AVDD), U11.6 (VDD); also elsewhere on the board
/Audio/OUT+: LS1.1, U11.5 (OUT+)
/Audio/OUT-: LS1.2, U11.8 (OUT-)
/Audio/RECORDED_SPEECH: C49.1, U9.1 (IN1P)
/BCLK: U9.7 (BCLK); also elsewhere on the board
/Digitalker/FILTERED_SPEECH: C49.2, C53.2, C55.2; also elsewhere on the board
/FSYNC: U9.8 (FSYNC); also elsewhere on the board
/SDATA: U9.6 (SDOUT); also elsewhere on the board
/~SPEAKER_DISABLE: U11.1 (~SD); also elsewhere on the board
GND: C36.2, C37.2, C38.2, C39.2, C40.2, C50.2, C51.2, C52.2, C54.2, C56.2, J5.S, R36.2, RV1.3, U9.5 (VSS), U9.10 (VSS), U9.11 (MD1), U9.12 (MD0), U9.13 (MSZ), U9.15 (VSS), U9.19 (FTM0), U9.20 (VSS), U9.21 (PAD), U11.7 (GND); also elsewhere on the board
unnamed: C53.1, RV1.1
unnamed: C55.1, R34.2, R35.2, R36.1
unnamed: J5.R, R34.1
unnamed: J5.T, R35.1
unnamed: C38.1, U9.17 (AREG)
unnamed: C37.1, U9.14 (DREG)
unnamed: C52.1, U9.2 (IN1M)
unnamed: C50.1, U9.4 (IN2M)
unnamed: C51.1, U9.3 (IN2P)
unnamed: C36.1, U9.18 (VREF)
unnamed: RV1.2, U11.3 (IN+)
unnamed: C56.1, U11.4 (IN-)

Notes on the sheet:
OUT TO EXTERRNAL SPEAKER AMPLIFIER
